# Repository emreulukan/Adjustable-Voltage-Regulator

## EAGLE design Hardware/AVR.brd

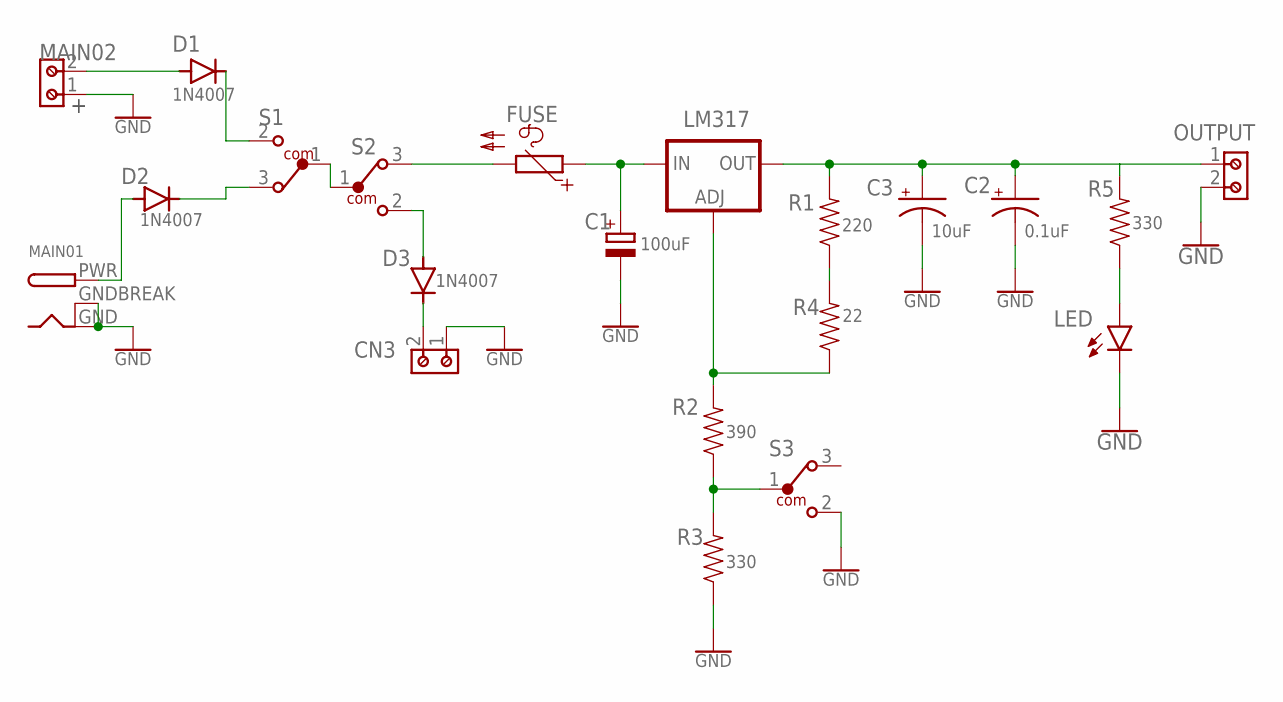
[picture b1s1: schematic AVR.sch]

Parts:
C1: 100uF; E2-5
C2: 0.1uF; E2,5-5
C3: 10uF; E2,5-5
CN3: 691211720002
D1, D2, D3: 1N4007; DO-41
FUSE: PTC660; P660
LED: LED3MM; LED_3MM
LM317: LM317; TO220-ADJ
MAIN01: DCBARRELPTH; DCJACK_2MM_PTH
MAIN02: 691211720002
OUTPUT: 691211720002
R1: 220; AXIAL-0.3
R2: 390; AXIAL-0.3
R3, R5: 330; AXIAL-0.3
R4: 22; AXIAL-0.3
S1, S2, S3: 450301014042

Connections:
GND: C1.-, C2.-, C3.-, CN3.1, LED.K (C), MAIN01.GND, MAIN01.GNDBREAK, MAIN02.1, OUTPUT.2, R3.P$1 (1), S3.2
unnamed: D1.A, MAIN02.2
unnamed: D2.A, MAIN01.PWR
unnamed: D1.C, S1.2
unnamed: D2.C, S1.3
unnamed: S1.1, S2.1
unnamed: FUSE.2, S2.3
unnamed: CN3.2, D3.C
unnamed: D3.A, S2.2
unnamed: C1.+, FUSE.1, LM317.IN
unnamed: C2.+, C3.+, LM317.OUT, OUTPUT.1, R1.P$2 (2), R5.P$2 (2)
unnamed: R1.P$1 (1), R4.P$2 (2)
unnamed: LM317.ADJ, R2.P$2 (2), R4.P$1 (1)
unnamed: R2.P$1 (1), R3.P$2 (2), S3.1
unnamed: LED.A, R5.P$1 (1)

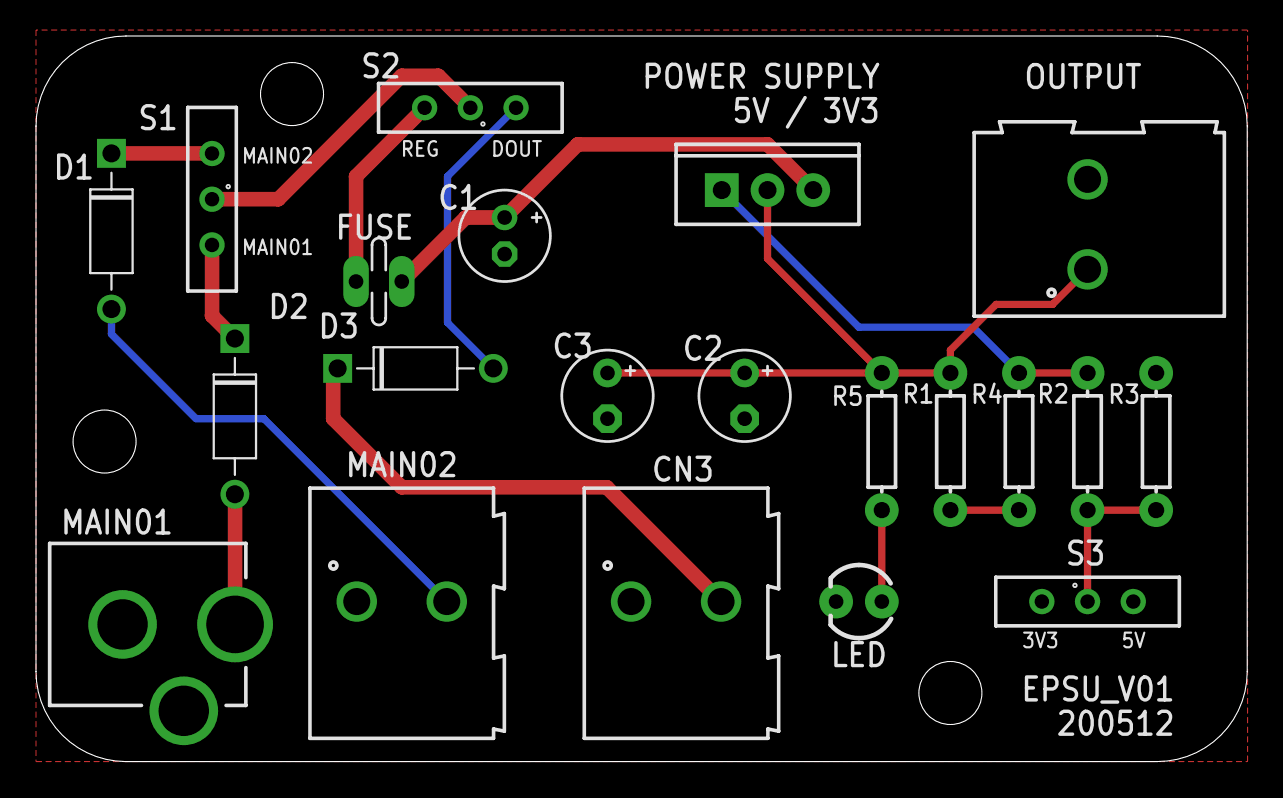
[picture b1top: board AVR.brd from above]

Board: 2 copper layers, 67.3 x 40.3 mm, 21 parts (0 on the bottom side), 15 nets.

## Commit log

2020-05-16 Hardware

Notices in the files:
parts and their libraries:
Wurth_Connectors_WR-TBL Rising Cage Clam: Copyright: Würth Elektronik
SparkFun-LED: Licensing: Creative Commons ShareAlike 4.0 International - https://creativecommons.org/licenses/by-sa/4.0
